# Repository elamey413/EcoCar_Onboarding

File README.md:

Hello! This is my onboardind project for the UAlberta club EcoCar. It contains an STM32F103C8T6 based PCB with an IMU, CAN transciever, thermocouple, and pressure sensor. It also has an OLED display to show all the amazing data you can collect
with the board. Please Download the Onboarding- Copy file to access the schematic and PCB model.

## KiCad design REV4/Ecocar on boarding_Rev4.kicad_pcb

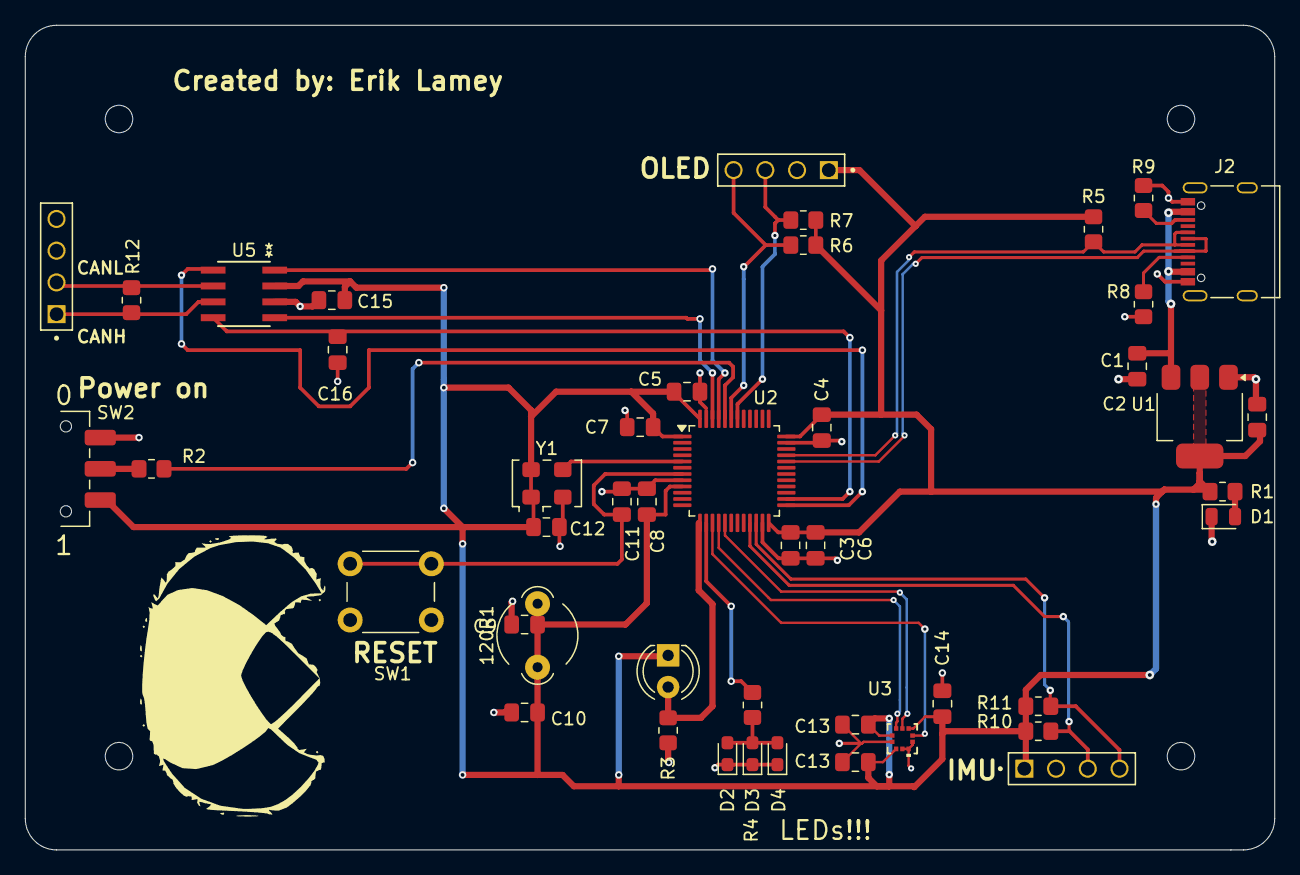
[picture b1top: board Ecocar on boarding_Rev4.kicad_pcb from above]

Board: 2 copper layers, 100.0 x 66.0 mm, 50 parts (0 on the bottom side), 29 nets.

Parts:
120R1: FerriteBead; LairdTech_28C0236-0JW-10
C1, C2: 22u; C_0805_2012Metric_Pad1.18x1.45mm_HandSolder
C3: 10u; C_0805_2012Metric_Pad1.18x1.45mm_HandSolder
C4, C5, C6, C7, C11, C12, C13, C13#2, C14, C15, C16: 100n; C_0805_2012Metric_Pad1.18x1.45mm_HandSolder
C8: 10n; C_0805_2012Metric_Pad1.18x1.45mm_HandSolder
C9, C10: 1u; C_0805_2012Metric_Pad1.18x1.45mm_HandSolder
D1: LED; LED_0805_2012Metric
D2: LED_R; LED_0603_1608Metric_Pad1.05x0.95mm_HandSolder
D3: LED_G; LED_0603_1608Metric_Pad1.05x0.95mm_HandSolder
D4: LED_B; LED_0603_1608Metric_Pad1.05x0.95mm_HandSolder
H1, H2, H3, H4: MountingHole; MountingHole_2.2mm_M2
J1, J3, J5: Conn_01x04_Socket; Conn_01x04_pin
J2: USB_C_Receptacle_USB2.0_16P; USB_C_Receptacle_Palconn_UTC16-G
R1, R4, R5: 1k5; R_0805_2012Metric_Pad1.20x1.40mm_HandSolder
R2: 10k; R_0805_2012Metric_Pad1.20x1.40mm_HandSolder
R3: 10K; R_0805_2012Metric_Pad1.20x1.40mm_HandSolder
R6, R7, R10, R11: 1K5; R_0805_2012Metric_Pad1.20x1.40mm_HandSolder
R8, R9: 5k1; R_0805_2012Metric_Pad1.20x1.40mm_HandSolder
R12: 120; R_0805_2012Metric_Pad1.20x1.40mm_HandSolder
SW1: SW_PUSH_6mm
SW2: SW_SPDT; SW_SPDT_CK_JS102011SAQN
TH1: 10K; LED_D4.0mm
U1: AMS1117-3.3; SOT-223-3_TabPin2
U2: STM32F103C8T6; LQFP-48_7x7mm_P0.5mm
U3: BME280; HLGA-10L_2X2X0P73_STM
U5: MCP2542FD; SOIC8_4P9X3P9MC_MCH
Y1: OT32258MJBA4SL; Oscillator_SMD_TXC_7C-4Pin_5.0x3.2mm

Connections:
+3.3VA: 120R1.2, C8.1, C9.1, U2.9 (VDDA)
+3V3: 120R1.1, C2.1, C3.1, C4.1, C5.1, C6.1, C7.1, C10.1, C12.1, C13.1, C13#2.1, C14.1, C15.1, J1.01, J3.01, R1.1, R5.1, R6.1, R7.1, R10.1, R11.1, SW2.3 (C), TH1.1, U1.2 (VO), U2.1 (VBAT), U2.24 (VDD), U2.36 (VDD), U2.48 (VDD), U3.3 (SDI), U3.6 (VDDIO), U3.8 (VDD), U5.3 (VCC), Y1.1 (EN), Y1.4 (Vdd)
/BOOT0: R2.2, U2.44 (BOOT0)
/CANH: J5.01, R12.1, U5.7 (CANH)
/CANL: J5.02, R12.2, U5.6 (CANL)
/CAN_RX: U2.45 (PB8), U5.4 (RXD)
/CAN_TX: U2.46 (PB9), U5.1 (TXD)
/CC1: J2.A5 (CC1), R8.1
/CC2: J2.B5 (CC2), R9.1
/HSE_in: U2.5 (PD0), Y1.3 (OUT)
/I2C1_SCL_OLED: J1.03, R7.2, U2.42 (PB6)
/I2C1_SDA_OLED: J1.04, R6.2, U2.43 (PB7)
/I2C2_SCL_IMU: J3.03, R10.2, U2.21 (PB10)
/I2C2_SDA_IMU: J3.04, R11.2, U2.22 (PB11)
/NRST: C11.1, SW1.1, U2.7 (NRST)
/PWR_LED_K: D1.2 (A), R1.2
/SPI_MISO: U2.16 (PA6), U3.5 (SDO)
/SPI_MOSI: U2.17 (PA7), U3.4 (SCK)
/SPI_SCK: U2.15 (PA5), U3.2 (CSB)
/STBY: U2.25 (PB12), U5.5 (SHDN)
/STD: C16.1, U2.26 (PB13), U5.8 (STD)
/SW_BOOT0: R2.1, SW2.2 (B)
/USB_D+: J2.A6 (D+), J2.B6 (D+), R5.2, U2.33 (PA12)
/USB_D-: J2.A7 (D-), J2.B7 (D-), U2.32 (PA11)
GND: C1.2, C2.2, C3.2, C4.2, C5.2, C6.2, C7.2, C8.2, C9.2, C10.2, C11.2, C12.2, C13.2, C13#2.2, C14.2, C15.2, C16.2, D1.1 (K), D2.1 (K), D3.1 (K), D4.1 (K), J1.02, J2.A1 (GND), J2.A12 (GND), J2.B1 (GND), J2.B12 (GND), J3.02, R3.2, R8.2, R9.2, SW1.2, SW2.1 (A), U1.1 (GND), U2.8 (VSSA), U2.23 (VSS), U2.35 (VSS), U2.47 (VSS), U3.1 (GND), U3.7 (GND), U3.9 (GND), U3.10 (GND), U5.2 (GND), Y1.2 (GND)
unnamed: D2.2 (A), D3.2 (A), D4.2 (A), R4.1
unnamed: R3.1, TH1.2, U2.13 (PA3)
unnamed: R4.2, U2.14 (PA4)
VBUS: C1.1, J2.A4 (VBUS), J2.A9 (VBUS), J2.B4 (VBUS), J2.B9 (VBUS), U1.3 (VI)

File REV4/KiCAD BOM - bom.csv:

Designator,Footprint,Quantity,Value,LCSC Part #
120R1,LairdTech_28C0236-0JW-10,1,FerriteBead 120R,
"C1, C2",805,2,22u,
"C10, C9",805,2,1u,
"C11, C12, C13_2, C13, C14, C15, C16, C4, C5, C6, C7",805,11,100n,
C3,805,1,10u,
C8,805,1,10n,
D1,805,1,LED,
"D2,D3,D4",603,3,LED_R,
J2,USB_C_Receptacle_Palconn_UTC16-G,1,USB_C_Receptacle_USB2.0_16P,
"R1, R10, R11, R4, R5, R6, R7",805,7,1k5,
R12,805,1,120,
"R2, R3",805,2,10k,
"R8, R9",805,2,5k1,
SW1,SW_PUSH_6mm,1,SW_PUSH_6mm,
SW2,SW_SPDT_CK_JS102011SAQN,1,SW_SPDT,
TH1,LED_D4.0mm,1,"10K, RL0503-5820-97-MS",https://www.digikey.ca/en/products/detail/amphenol-advanced-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
U1,SOT-223-3_TabPin2,1,AMS1117-3.3,
U3,HLGA-10L_2X2X0P73_STM,1,BME280,
U5,SOIC8_4P9X3P9MC_MCH,1,MCP2542FD,
Y1,Oscillator_SMD_TXC_7C-4Pin_5.0x3.2mm,1,OT32258MJBA4SL,
,,,,
Parts On hand,,,,
U2,LQFP-48_7x7mm_P0.5mm,1,STM32F103C8T6,
U4,None,1,IMU GY 521,
U6,,1,NHD-C0220BIZ,

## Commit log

2025-10-25 Pushing KiCAD file v1
2025-10-25 Pushing Onboarding V2
2025-10-29 Revision 2 upload
2025-10-30 Revision 3 Upload
2025-11-01 Revision 4 upload
2025-11-01 Complete Bom upload
